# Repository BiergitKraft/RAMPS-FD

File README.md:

# RAMPS-FD

RAMPS for Due.

A RAMPS style Shield for Arduino Due to benefit from the 32bit uC combined with the modular Design of a RAMPS Board.
V2.3 adds SPI support by simply selecting it with a few jumpers.
V3.0 adds UART support. WIP

Status
-------

V2.3 tested and fuctional.
V3.0 WIP

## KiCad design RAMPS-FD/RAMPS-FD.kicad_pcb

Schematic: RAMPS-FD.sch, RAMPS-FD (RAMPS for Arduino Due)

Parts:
D2: LED_0603_GREEN; LED_0603
FID2, FID3, FID4: Fiducial; Fiducial_1mm_Mask2mm
J2: 2x1PinHeader; PinHeader_1x02_P2.54mm_Vertical
M2: LOGO_OSHW; OSHW_logo_2
Q2: NCE3416; SOT-23; Rating #20V #6.5A
R2: 330R; R_0603
SHIELD2: ARDUINO_DUE_SHIELD; ARDUINO_MEGA_DUE_SHIELD_FOOTPRINT_RMC
SW2: PushButton; SW_6x6_SMD

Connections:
+3V3: SHIELD2.3V3
+5V: D2.2; also elsewhere on the board
/E0_EN_BUF: SHIELD2.42; also elsewhere on the board
/E1_EN_BUF: SHIELD2.39; also elsewhere on the board
/E2_EN_BUF: SHIELD2.45; also elsewhere on the board
/RESET: J2.1, SHIELD2.RST, SW2.1
/X_EN_BUF: SHIELD2.48; also elsewhere on the board
/Y_EN_BUF: SHIELD2.46; also elsewhere on the board
/Z_EN_BUF: SHIELD2.44; also elsewhere on the board
A4: SHIELD2.AD4; also elsewhere on the board
A5: SHIELD2.AD5; also elsewhere on the board
A6: SHIELD2.AD6; also elsewhere on the board
A7: SHIELD2.AD7; also elsewhere on the board
AD14: SHIELD2.AD14; also elsewhere on the board
AD15: SHIELD2.AD15; also elsewhere on the board
AM-VIN: SHIELD2.V_IN; also elsewhere on the board
D2-FET6: SHIELD2.2; also elsewhere on the board
D8: SHIELD2.8; also elsewhere on the board
D9: SHIELD2.9; also elsewhere on the board
D10: SHIELD2.10; also elsewhere on the board
D11-FET4: SHIELD2.11; also elsewhere on the board
D12-FET5: SHIELD2.12; also elsewhere on the board
D13: Q2.1, SHIELD2.13
D23: SHIELD2.23; also elsewhere on the board
D25: SHIELD2.25; also elsewhere on the board
D27: SHIELD2.27; also elsewhere on the board
D29: SHIELD2.29; also elsewhere on the board
D31: SHIELD2.31; also elsewhere on the board
D32: SHIELD2.32; also elsewhere on the board
D33: SHIELD2.33; also elsewhere on the board
D35: SHIELD2.35; also elsewhere on the board
D37: SHIELD2.37; also elsewhere on the board
D41: SHIELD2.41; also elsewhere on the board
D43: SHIELD2.43; also elsewhere on the board
D47: SHIELD2.47; also elsewhere on the board
D49: SHIELD2.49; also elsewhere on the board
D50-MISO: SHIELD2.50; also elsewhere on the board
D51-MOSI: SHIELD2.51; also elsewhere on the board
D52-SCK: SHIELD2.52; also elsewhere on the board
DUE_5V: SHIELD2.5V; also elsewhere on the board
E0_DIR: SHIELD2.28; also elsewhere on the board
E0_STEP: SHIELD2.36; also elsewhere on the board
ESTOP: SHIELD2.40; also elsewhere on the board
GND: J2.2, Q2.2, SHIELD2.GND, SHIELD2.GND6, SW2.2; also elsewhere on the board
GNDA: SHIELD2.GND4, SHIELD2.GND5; also elsewhere on the board
IOREF: SHIELD2.IORF; also elsewhere on the board
MISO: SHIELD2.MISO; also elsewhere on the board
MOSI: SHIELD2.MOSI; also elsewhere on the board
unnamed: D2.1, R2.1
unnamed: Q2.3, R2.2
PS-ON: SHIELD2.53; also elsewhere on the board
SCK: SHIELD2.SCK; also elsewhere on the board
SCL: SHIELD2.21; also elsewhere on the board
SCL1: SHIELD2.SCL1; also elsewhere on the board
SDA: SHIELD2.20; also elsewhere on the board
SDA1: SHIELD2.SDA1; also elsewhere on the board
SERVO1: SHIELD2.7; also elsewhere on the board
SERVO2: SHIELD2.6; also elsewhere on the board
SERVO3: SHIELD2.5; also elsewhere on the board
SERVO4: SHIELD2.3; also elsewhere on the board
SPI_CS1: SHIELD2.4; also elsewhere on the board
THERM0: SHIELD2.AD0; also elsewhere on the board
THERM1: SHIELD2.AD1; also elsewhere on the board
THERM2: SHIELD2.AD2; also elsewhere on the board
THERM3: SHIELD2.AD3; also elsewhere on the board
UART0_RX_LV: SHIELD2.0; also elsewhere on the board
UART0_TX_LV: SHIELD2.1; also elsewhere on the board
UART1_RX_LV: SHIELD2.19; also elsewhere on the board
UART1_TX_LV: SHIELD2.18; also elsewhere on the board
UART2_RX_LV: SHIELD2.17; also elsewhere on the board
UART2_TX_LV: SHIELD2.16; also elsewhere on the board
UART3_RX_LV: SHIELD2.15; also elsewhere on the board
UART3_TX_LV: SHIELD2.14; also elsewhere on the board
X-MAX: SHIELD2.30; also elsewhere on the board
X-MIN: SHIELD2.22; also elsewhere on the board
X_DIR: SHIELD2.AD8; also elsewhere on the board
X_STEP: SHIELD2.AD9; also elsewhere on the board
Y-MAX: SHIELD2.38; also elsewhere on the board
Y-MIN: SHIELD2.24; also elsewhere on the board
Y_DIR: SHIELD2.AD10; also elsewhere on the board
Y_STEP: SHIELD2.AD11; also elsewhere on the board
Z-MAX: SHIELD2.34; also elsewhere on the board
Z-MIN: SHIELD2.26; also elsewhere on the board
Z_DIR: SHIELD2.AD12; also elsewhere on the board
Z_STEP: SHIELD2.AD13; also elsewhere on the board

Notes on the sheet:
Also used by Programming USB port
X/Y/Z pins are on single port for both Mega and Due
Reset
Status LED
LED

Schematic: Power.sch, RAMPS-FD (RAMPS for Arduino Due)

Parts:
C2: 100u_35V; CP_Elec_6.3x7.7; Rating #100uF #35V #20%
C3, C4: 100n; C_0603; Rating #100nF #50V #5%
D3, D4: KDZVTR11B; D_SOD-123F
D5: MRA4003T3G; D_SMA; Rating #300V #1A
F2, F3, F4: Keystone_3568; Fuseholder_Blade_Mini_Keystone_3568; Rating #500V #30A
F5, F6: FUSE_750mA_0603; R_0603; Rating #32V #750mA
J3: 6_PinScrewPlugableTerminal_P508; 6x1_P508_RA
J4: NetTie_1mm; TIE-1MM
J5, J7: 1x3JumperArray; PinHeader_1x03_P2.54mm_Vertical
J6: 2x1PinHeader; PinHeader_1x02_P2.54mm_Vertical
J8: 1x3PinHeader; PinHeader_1x03_P2.54mm_Vertical
JP2, JP3: 1x2JumperArray; PinHeader_1x02_P2.54mm_Vertical
Q3, Q4: TDM3415; SO-8_3.9x4.9mm_P1.27mm
R3, R4: 10k; R_0603
U2: AS7812ADTR; TO-252-2; Rating #12V #35V #1A

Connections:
+5V: J7.3, J8.1, JP3.2; also elsewhere on the board
+12P: D5.2, J5.2, J6.1; also elsewhere on the board
+V_HEATBED: F2.2; also elsewhere on the board
+V_LOGIC: J7.2; also elsewhere on the board
+V_MOTOR: D3.1, Q3.1, Q3.2, Q3.3; also elsewhere on the board
+V_POWER: C2.1, C3.1, D4.1, J5.3, Q4.1, Q4.2, Q4.3, U2.1; also elsewhere on the board
/Power/HB_IN: F2.1, J3.1
/Power/LP_1: D5.1, JP2.1
/Power/LP_2: C4.1, J5.1, U2.3
/Power/MOT_IN: F3.1, J3.5
/Power/P_IN: F4.1, J3.3
AM-VIN: JP2.2; also elsewhere on the board
DUE_5V: F6.2; also elsewhere on the board
GND: J6.2, J8.3; also elsewhere on the board
IOREF: F5.2; also elsewhere on the board
MOT_GND: C2.2, C3.2, C4.2, J3.2, J3.4, J3.6, R3.2, R4.2, U2.2; also elsewhere on the board
unnamed: D3.2, Q3.4, R3.1
unnamed: D4.2, Q4.4, R4.1
unnamed: F3.2, Q3.5, Q3.6, Q3.7, Q3.8
unnamed: F4.2, Q4.5, Q4.6, Q4.7, Q4.8
unnamed: F5.1, J7.1
unnamed: F6.1, JP3.1
PS-ON: J8.2; also elsewhere on the board

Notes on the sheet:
JP102 - VSEL - Select voltage 1-2 = POWER_IN = 24 V (or > 15V) 2-3 = POWER_IN = 12 V (or < 15V)
Low power MOSFETS (fans etc) also input to Due/Mega
Aux Power output
VLOG - Select logic voltage 1-2 = Autoselect by IOREF 2-3 = 5V
Medium power MOSFETS (extruder heaters, fans)
Heatbed Only: 12-24V, 15A
Motors only, 12-24V
Power
JP1: Supply 12V to Arduino in standalone operation Remove if Arduino is powered by USB or other supply
Note: use thick traces for all high power connections
12V or 24V input (ensure to set JP102 correctly!)
5V: External or Standby
Arduino base board
Note: On R3 compatible Arduinos, IOREF will supply 3.3V (Due), or 5V (Mega). If IOREF is not provided (non-R3) then it must be a 5V Arduino so set VLOG to 5V.
Capacitors rated to at least 25V unless otherwise stated

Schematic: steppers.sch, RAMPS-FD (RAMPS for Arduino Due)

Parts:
C5, C6, C7: 100u_35V; CP_Elec_6.3x7.7; Rating #100uF #35V #20%
D6, D8, D10: DS110W; D_SOD-123F
D7, D9, D11: SMF36CA; D_SOD-123F
J9, J10, J11, J12: 1x4PinHeader; pin_header_2.54mm_1x4
JP4, JP6, JP8: 4x3JumperArray; 4x3_2.54mm_Header
JP5, JP7, JP9: 1x2JumperArray; PinHeader_1x02_P2.54mm_Vertical
R5: 1k; R_0603
R6, R8, R10: 10k; R_0603
R7, R9, R11: 100k; R_0603
U3, U4, U5: Pololu; POLOLU
VR2, VR3, VR4, VR5, VR6, VR7, VR8, VR9, VR10, VR11, VR12, VR13, VR14, VR15, VR16, VR17, VR18, VR19: 33V; R_0603

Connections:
+5V: D6.2, D8.2, D10.2; also elsewhere on the board
+V_LOGIC: JP4.3, JP4.6, JP4.9, JP4.12, JP6.3, JP6.6, JP6.9, JP6.12, JP8.3, JP8.6, JP8.9, JP8.12, R6.1, R8.1, R10.1, U3.10, U4.10, U5.10; also elsewhere on the board
+V_MOTOR: C5.1, C6.1, C7.1, D6.1, D7.1, D8.1, D9.1, D10.1, D11.1, U3.16, U4.16, U5.16; also elsewhere on the board
/Stepper Drivers/X-1A: J9.3, U3.12, VR3.1, VR6.1
/Stepper Drivers/X-1B: J9.4, U3.11, VR3.2, VR7.1
/Stepper Drivers/X-2A: J9.2, U3.13, VR2.2, VR4.1
/Stepper Drivers/X-2B: J9.1, U3.14, VR2.1, VR5.1
/Stepper Drivers/Y-1A: J10.3, U4.12, VR10.1, VR13.1
/Stepper Drivers/Y-1B: J10.4, U4.11, VR11.1, VR13.2
/Stepper Drivers/Y-2A: J10.2, U4.13, VR8.1, VR12.2
/Stepper Drivers/Y-2B: J10.1, U4.14, VR9.1, VR12.1
/Stepper Drivers/Z-1A: J11.3, J12.3, U5.12, VR16.1, VR19.1
/Stepper Drivers/Z-1B: J11.4, J12.4, U5.11, VR17.1, VR19.2
/Stepper Drivers/Z-2A: J11.2, J12.2, U5.13, VR14.1, VR18.2
/Stepper Drivers/Z-2B: J11.1, J12.1, U5.14, VR15.1, VR18.1
/X_EN_BUF: U3.1; also elsewhere on the board
/Y_EN_BUF: U4.1; also elsewhere on the board
/Z_EN_BUF: U5.1; also elsewhere on the board
A6: JP8.7; also elsewhere on the board
A7: JP6.7; also elsewhere on the board
AD15: JP4.7; also elsewhere on the board
D50-MISO: JP4.10, JP6.10, JP8.10; also elsewhere on the board
D51-MOSI: JP4.1, JP6.1, JP8.1; also elsewhere on the board
D52-SCK: JP4.4, JP6.4, JP8.4; also elsewhere on the board
GND: R7.2, R9.2, R11.2, U3.9, U4.9, U5.9; also elsewhere on the board
MOT_GND: C5.2, C6.2, C7.2, D7.2, D9.2, D11.2, U3.15, U4.15, U5.15, VR4.2, VR5.2, VR6.2, VR7.2, VR8.2, VR9.2, VR10.2, VR11.2, VR14.2, VR15.2, VR16.2, VR17.2; also elsewhere on the board
unnamed: JP4.2, R7.1, U3.2
unnamed: JP4.5, U3.3
unnamed: JP4.8, U3.4
unnamed: JP4.11, JP5.2, U3.5
unnamed: JP6.2, R9.1, U4.2
unnamed: JP6.5, U4.3
unnamed: JP6.8, U4.4
unnamed: JP6.11, JP7.2, U4.5
unnamed: JP8.2, R11.1, U5.2
unnamed: JP8.5, U5.3
unnamed: JP8.8, U5.4
unnamed: JP8.11, JP9.2, U5.5
unnamed: R6.2, U3.6
unnamed: R8.2, U4.6
unnamed: R10.2, U5.6
UART1_RX_LV: JP5.1, JP7.1, JP9.1, R5.1; also elsewhere on the board
UART1_TX_LV: R5.2; also elsewhere on the board
X_DIR: U3.8; also elsewhere on the board
X_STEP: U3.7; also elsewhere on the board
Y_DIR: U4.8; also elsewhere on the board
Y_STEP: U4.7; also elsewhere on the board
Z_DIR: U5.8; also elsewhere on the board
Z_STEP: U5.7; also elsewhere on the board

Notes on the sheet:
Add jumpers for TMC2130 SPI
Use Jumpers to Connect the SPI Bus to your Stepperdrivers, for example for TMC 2130, or to select the microstepping for your Pololu by connecting the middle pin row to +V_Logic

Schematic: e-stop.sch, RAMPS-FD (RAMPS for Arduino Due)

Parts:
C8: 100n; C_0603; Rating #100nF #50V #5%
D12: 2CZ4007; D_SOD-123F; Rating #1kV #1A
D13: LED_0603_GREEN; LED_0603
J13: 2x1PinHeader; PinHeader_1x02_P2.54mm_Vertical
Q5: NCE3416; SOT-23; Rating #20V #6.5A
R12: 100k; R_0603
R13: 4k7; R_0603
R14: 330R; R_0603
RP2, RP3, RP4: 10kArrayx4; R_Array_Convex_4x0603
U6: SN74LV1T125; SOT-23-5

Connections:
+5V: C8.1, R14.1, U6.5; also elsewhere on the board
+V_LOGIC: R12.1, RP2.5, RP2.6, RP2.7, RP2.8, RP3.7, RP3.8; also elsewhere on the board
/E0_EN_BUF: RP2.4; also elsewhere on the board
/E1_EN_BUF: RP3.1; also elsewhere on the board
/E2_EN_BUF: RP3.2; also elsewhere on the board
/X_EN_BUF: RP2.1; also elsewhere on the board
/Y_EN_BUF: RP2.2; also elsewhere on the board
/Z_EN_BUF: RP2.3; also elsewhere on the board
D2-FET6: RP4.8; also elsewhere on the board
D8: RP3.4, U6.2; also elsewhere on the board
D8_BUF: U6.4; also elsewhere on the board
D9: RP3.3; also elsewhere on the board
D10: RP4.7; also elsewhere on the board
D11-FET4: RP4.6; also elsewhere on the board
D12-FET5: RP4.5; also elsewhere on the board
ESTOP: D12.1; also elsewhere on the board
GND: C8.2, Q5.2, R13.2, RP3.5, RP3.6, RP4.1, RP4.2, RP4.3, RP4.4, U6.3; also elsewhere on the board
unnamed: D12.2, J13.1, Q5.1, R12.2, U6.1
unnamed: D13.1, Q5.3
unnamed: D13.2, R14.2
unnamed: J13.2, R13.1

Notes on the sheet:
Emergency Stop switch (Normally Closed type) use jumper to bypass
Or any small signal diode
Active low
Active high
Use a Buffer to translate the 3V3 Signal of the Due to 5V to fully open the Mosfet Possible alternative parts (pin compatible): 74LVC1G17 SN74LV1T34

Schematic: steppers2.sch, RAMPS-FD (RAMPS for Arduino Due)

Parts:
C9, C10, C11: 100u_35V; CP_Elec_6.3x7.7; Rating #100uF #35V #20%
D14, D16, D18: DS110W; D_SOD-123F
D15, D17, D19: SMF36CA; D_SOD-123F
J14, J15, J16: 1x4PinHeader; pin_header_2.54mm_1x4
JP10, JP12, JP14: 4x3JumperArray; 4x3_2.54mm_Header
JP11, JP13, JP15: 1x2JumperArray; PinHeader_1x02_P2.54mm_Vertical
R15: 1k; R_0603
R16, R18, R20: 10k; R_0603
R17, R19, R21: 100k; R_0603
U7, U8, U9: Pololu; POLOLU
VR20, VR21, VR22, VR23, VR24, VR25, VR26, VR27, VR28, VR29, VR30, VR31, VR32, VR33, VR34, VR35, VR36, VR37: 33V; R_0603

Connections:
+5V: D14.2, D16.2, D18.2; also elsewhere on the board
+V_LOGIC: JP10.3, JP10.6, JP10.9, JP10.12, JP12.3, JP12.6, JP12.9, JP12.12, JP14.3, JP14.6, JP14.9, JP14.12, R16.1, R18.1, R20.1, U7.10, U8.10, U9.10; also elsewhere on the board
+V_MOTOR: C9.1, C10.1, C11.1, D14.1, D15.1, D16.1, D17.1, D18.1, D19.1, U7.16, U8.16, U9.16; also elsewhere on the board
/E0_EN_BUF: U7.1; also elsewhere on the board
/E1_EN_BUF: U8.1; also elsewhere on the board
/E2_EN_BUF: U9.1; also elsewhere on the board
/Stepper Drivers 2/E0-1A: J14.3, U7.12, VR21.1, VR24.1
/Stepper Drivers 2/E0-1B: J14.4, U7.11, VR21.2, VR25.1
/Stepper Drivers 2/E0-2A: J14.2, U7.13, VR20.2, VR22.1
/Stepper Drivers 2/E0-2B: J14.1, U7.14, VR20.1, VR23.1
/Stepper Drivers 2/E1-1A: J15.3, U8.12, VR27.1, VR30.1
/Stepper Drivers 2/E1-1B: J15.4, U8.11, VR27.2, VR31.1
/Stepper Drivers 2/E1-2A: J15.2, U8.13, VR26.2, VR29.1
/Stepper Drivers 2/E1-2B: J15.1, U8.14, VR26.1, VR28.1
/Stepper Drivers 2/E2-1A: J16.3, U9.12, VR34.1, VR37.1
/Stepper Drivers 2/E2-1B: J16.4, U9.11, VR35.1, VR37.2
/Stepper Drivers 2/E2-2A: J16.2, U9.13, VR33.1, VR36.2
/Stepper Drivers 2/E2-2B: J16.1, U9.14, VR32.1, VR36.1
A4: JP10.7; also elsewhere on the board
A5: JP12.7; also elsewhere on the board
AD14: JP14.7; also elsewhere on the board
D32: U9.7; also elsewhere on the board
D41: U8.8; also elsewhere on the board
D43: U8.7; also elsewhere on the board
D47: U9.8; also elsewhere on the board
D50-MISO: JP10.10, JP12.10, JP14.10; also elsewhere on the board
D51-MOSI: JP10.1, JP12.1, JP14.1; also elsewhere on the board
D52-SCK: JP10.4, JP12.4, JP14.4; also elsewhere on the board
E0_DIR: U7.8; also elsewhere on the board
E0_STEP: U7.7; also elsewhere on the board
GND: R17.2, R19.2, R21.2, U7.9, U8.9, U9.9; also elsewhere on the board
MOT_GND: C9.2, C10.2, C11.2, D15.2, D17.2, D19.2, U7.15, U8.15, U9.15, VR22.2, VR23.2, VR24.2, VR25.2, VR28.2, VR29.2, VR30.2, VR31.2, VR32.2, VR33.2, VR34.2, VR35.2; also elsewhere on the board
unnamed: JP10.2, R17.1, U7.2
unnamed: JP10.5, U7.3
unnamed: JP10.8, U7.4
unnamed: JP10.11, JP11.2, U7.5
unnamed: JP12.2, R19.1, U8.2
unnamed: JP12.5, U8.3
unnamed: JP12.8, U8.4
unnamed: JP12.11, JP13.2, U8.5
unnamed: JP14.2, R21.1, U9.2
unnamed: JP14.5, U9.3
unnamed: JP14.8, U9.4
unnamed: JP14.11, JP15.2, U9.5
unnamed: R16.2, U7.6
unnamed: R18.2, U8.6
unnamed: R20.2, U9.6
UART1_RX_LV: JP11.1; also elsewhere on the board
UART2_RX_LV: JP13.1, JP15.1, R15.2; also elsewhere on the board
UART2_TX_LV: R15.1; also elsewhere on the board

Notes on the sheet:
Add jumpers for TMC2130 SPI
Use Jumpers to Connect the SPI Bus to your Stepperdrivers, for example for TMC 2130, or to select the microstepping for your Pololu by connecting the middle pin row to +V_Logic

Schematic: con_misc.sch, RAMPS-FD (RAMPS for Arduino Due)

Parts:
C12: 100n; C_0603; Rating #100nF #50V #5%
J17, J20: 1x3PinHeader; PinHeader_1x03_P2.54mm_Vertical
J18: 2x5PinHeader; pin_header_2.54mm_2x5
J19, J22: 1x4PinHeader; pin_header_2.54mm_1x4
J21: 2x6PinHeader; pin_header_2.54mm_2x6
J23: 3x4PinHeader; 4x3_2.54mm_Header
J24: 1x18PinHeader; PinHeader_1x18_P2.54mm_Vertical
R22, R23, R24, R25: 10k; R_0603
U10: 24C512; SOIC-8_3.9x4.9mm_P1.27mm

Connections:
+5V: J21.1, J23.2, J23.5, J23.8, J23.11; also elsewhere on the board
+V_LOGIC: C12.1, J18.1, J19.1, J21.12, J22.1, J24.1, R22.1, R23.1, R24.1, R25.1, U10.8 (VCC); also elsewhere on the board
/E1_EN_BUF: J24.8; also elsewhere on the board
/E2_EN_BUF: J24.5; also elsewhere on the board
A4: J18.3; also elsewhere on the board
A5: J18.4; also elsewhere on the board
A6: J18.5; also elsewhere on the board
A7: J18.6; also elsewhere on the board
AD14: J18.7; also elsewhere on the board
AD15: J18.8; also elsewhere on the board
D23: J24.16; also elsewhere on the board
D25: J24.15; also elsewhere on the board
D27: J24.14; also elsewhere on the board
D29: J24.13; also elsewhere on the board
D31: J24.12; also elsewhere on the board
D32: J24.3; also elsewhere on the board
D33: J24.11; also elsewhere on the board
D35: J24.10; also elsewhere on the board
D37: J24.9; also elsewhere on the board
D41: J24.7; also elsewhere on the board
D43: J24.6; also elsewhere on the board
D47: J24.4; also elsewhere on the board
D49: J21.2; also elsewhere on the board
D50-MISO: J21.9; also elsewhere on the board
D51-MOSI: J21.10; also elsewhere on the board
D52-SCK: J21.11; also elsewhere on the board
GND: C12.2, J17.1, J18.2, J19.2, J20.1, J21.7, J22.2, J23.1, J23.4, J23.7, J23.10, J24.2, U10.1 (A0), U10.2 (A1), U10.3 (A2), U10.4 (GND), U10.7 (WP); also elsewhere on the board
MISO: J21.3; also elsewhere on the board
MOSI: J21.4; also elsewhere on the board
SCK: J21.5; also elsewhere on the board
SCL: J19.4, R22.2, U10.6 (SCL); also elsewhere on the board
SCL1: J22.4, R24.2; also elsewhere on the board
SDA: J19.3, R23.2, U10.5 (SDA); also elsewhere on the board
SDA1: J22.3, R25.2; also elsewhere on the board
SERVO1: J23.3; also elsewhere on the board
SERVO2: J23.6; also elsewhere on the board
SERVO3: J23.9; also elsewhere on the board
SERVO4: J23.12; also elsewhere on the board
SPI_CS1: J21.6; also elsewhere on the board
UART0_RX_LV: J17.2; also elsewhere on the board
UART0_TX_LV: J17.3; also elsewhere on the board
UART1_RX_LV: J20.2; also elsewhere on the board
UART1_TX_LV: J20.3; also elsewhere on the board
UART2_RX_LV: J24.17; also elsewhere on the board
UART2_TX_LV: J24.18; also elsewhere on the board
UART3_RX_LV: J18.10; also elsewhere on the board
UART3_TX_LV: J18.9; also elsewhere on the board

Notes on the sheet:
Serial
UART-TTL
Must not have external pullups to 5V if IOREF = 3.3V
1k5 Pull ups on Due
Aux3 - SPI
Aux2
Aux connectors
Servos
I2C
NB: On Arduino Due: IOs on this page are not 5V tolerant. Do not exceed 3.3V.
Note: this serial port is shared with USB programming port
These are shared with E1 and E2 stepper signals
Mega: same signals as MISO, MOSI & SCK
NB This pin is always 5V
These are free for LCD panel etc
Note: Some addon boards connect this pin to GND.
EEPROM
Might want to allow other addresses
Aux4 - general IO

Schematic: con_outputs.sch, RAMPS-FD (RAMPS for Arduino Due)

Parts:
D20, D21, D24, D25: MRA4003T3G; D_SMA; Rating #300V #1A
D22, D23, D26, D27: LED_0603_RED; LED_0603
J25, J27, J28: 2_PinScrewTerminal_P350; 2x1_P350
J26: 2_PinScrewTerminal_P508; 2x1_P508
Q6, Q8, Q9: PSMN7R5-60YLX; LFPAK56; Rating #60V #86A
Q7: PSMN1R8-40YLC; LFPAK56; Rating #40V #100A
R26, R27, R30, R31: 1k; R_0603
R28, R29, R32, R33: 33R; R_0603

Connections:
+V_HEATBED: D21.1, J26.1, R27.1; also elsewhere on the board
+V_POWER: D20.1, D24.1, D25.1, J25.1, J27.1, J28.1, R26.1, R30.1, R31.1; also elsewhere on the board
/Mosfet Outputs/D8_OUT: D21.2, D23.1, J26.2, Q7.5
/Mosfet Outputs/D9_OUT: D24.2, D26.1, J27.2, Q9.5
/Mosfet Outputs/D10_OUT: D25.2, D27.1, J28.2, Q8.5
/Mosfet Outputs/FET4_OUT: D20.2, D22.1, J25.2, Q6.5
D8_BUF: R29.1; also elsewhere on the board
D9: R33.1; also elsewhere on the board
D10: R32.1; also elsewhere on the board
D11-FET4: R28.1; also elsewhere on the board
MOT_GND: Q6.1, Q6.2, Q6.3, Q7.1, Q7.2, Q7.3, Q8.1, Q8.2, Q8.3, Q9.1, Q9.2, Q9.3; also elsewhere on the board
unnamed: D22.2, R26.2
unnamed: D23.2, R27.2
unnamed: D26.2, R30.2
unnamed: D27.2, R31.2
unnamed: Q6.4, R28.2
unnamed: Q7.4, R29.2
unnamed: Q8.4, R32.2
unnamed: Q9.4, R33.2

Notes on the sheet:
FET4 - Extruder 3 / Fan
D10 - Extruder 2 / Fan
D9 - Extruder 1
D8 - Heatbed
Non-inverting drivers
MOSFET Outputs
Or similar

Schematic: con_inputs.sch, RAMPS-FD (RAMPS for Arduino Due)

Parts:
C13: 100n; C_0603; Rating #100nF #50V #5%
J29: 3x6PinHeader; 6x3_2.54mm_Header
JP16: 1x2JumperArray; PinHeader_1x02_P2.54mm_Vertical
RP5, RP6: 10kArrayx4; R_Array_Convex_4x0603
U11: MC74LCX07; TSSOP-14_4.4x5mm_P0.65mm

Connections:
+5V: J29.1, J29.4, J29.7, J29.10, J29.13, J29.16, JP16.1; also elsewhere on the board
+V_LOGIC: C13.1, U11.14; also elsewhere on the board
GND: C13.2, J29.3, J29.6, J29.9, J29.12, J29.15, J29.18, U11.7; also elsewhere on the board
unnamed: J29.2, RP5.4, U11.1
unnamed: J29.5, RP5.3, U11.3
unnamed: J29.8, RP5.2, U11.5
unnamed: J29.11, RP6.3, U11.13
unnamed: J29.14, RP6.2, U11.11
unnamed: J29.17, RP6.1, U11.9
unnamed: JP16.2, RP5.5, RP5.6, RP5.7, RP5.8, RP6.5, RP6.6, RP6.7, RP6.8
X-MAX: U11.10; also elsewhere on the board
X-MIN: U11.8; also elsewhere on the board
Y-MAX: U11.6; also elsewhere on the board
Y-MIN: U11.12; also elsewhere on the board
Z-MAX: U11.2; also elsewhere on the board
Z-MIN: U11.4; also elsewhere on the board

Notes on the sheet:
Endstop inputs are 5V tolerant
Endstops
JP801 should be used to enable pullups for switch type endstops; remove for active types (e.g opto)

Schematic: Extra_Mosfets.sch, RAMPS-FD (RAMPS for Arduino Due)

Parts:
D28, D30: 2CZ4007; D_SOD-123F; Rating #1kV #1A
D29, D31: LED_0603_RED; LED_0603
J30, J31: 2x1PinHeader; PinHeader_1x02_P2.54mm_Vertical
Q10, Q11: NCE3416; SOT-23; Rating #20V #6.5A
R34, R36: 1k; R_0603
R35, R37: 33R; R_0603

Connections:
+12P: D28.1, D30.1, J30.1, J31.1, R34.1, R36.1; also elsewhere on the board
/Extra MOSFETs/P_FET5: D28.2, D29.1, J30.2, Q10.3
/Extra MOSFETs/P_FET6: D30.2, D31.1, J31.2, Q11.3
D2-FET6: R37.1; also elsewhere on the board
D12-FET5: R35.1; also elsewhere on the board
MOT_GND: Q10.2, Q11.2; also elsewhere on the board
unnamed: D29.2, R34.2
unnamed: D31.2, R36.2
unnamed: Q10.1, R35.2
unnamed: Q11.1, R37.2

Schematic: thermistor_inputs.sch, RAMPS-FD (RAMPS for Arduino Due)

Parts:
C14, C16, C18, C20: 100n; C_0603; Rating #100nF #50V #5%
C15, C17, C19, C21: 10u; C_0603; Rating #10uF #25V #10%
FB2: FB0603; R_0603; Rating #500mA #390Ohm@100MHz
J32: 2x4PinHeader_2.54mm; pin_header_2.54mm_2x4
R38, R39, R40, R41: 1k; R_0603

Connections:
+V_LOGIC: FB2.1; also elsewhere on the board
AREF: FB2.2, R38.1, R39.1, R40.1, R41.1
GNDA: C14.2, C15.2, C16.2, C17.2, C18.2, C19.2, C20.2, C21.2, J32.1, J32.3, J32.5, J32.7; also elsewhere on the board
THERM0: C14.1, C15.1, J32.2, R38.2; also elsewhere on the board
THERM1: C16.1, C17.1, J32.4, R39.2; also elsewhere on the board
THERM2: C18.1, C19.1, J32.6, R40.2; also elsewhere on the board
THERM3: C20.1, C21.1, J32.8, R41.2; also elsewhere on the board

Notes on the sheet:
To CPU
From thermistors
Thermistor Inputs

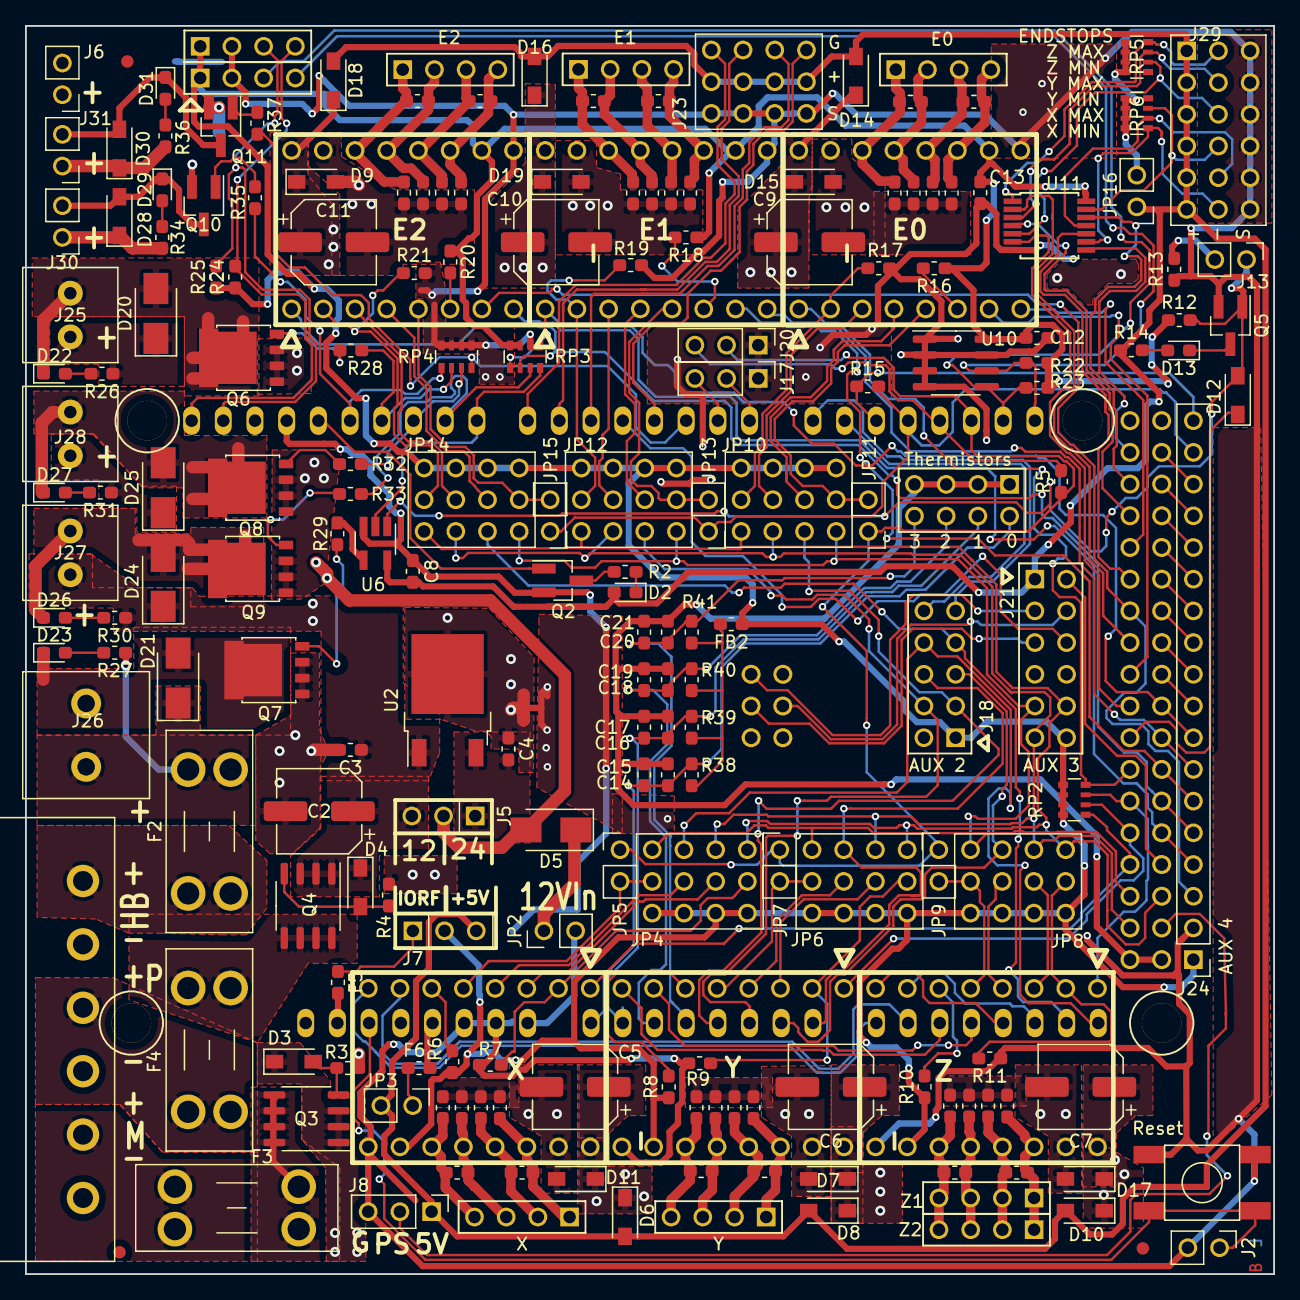
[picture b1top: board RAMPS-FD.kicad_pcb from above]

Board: 2 copper layers, 100.0 x 100.0 mm, 209 parts (1 on the bottom side), 186 nets.

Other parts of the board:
NT1: NetTie-2_SMD_Pad0.5mm

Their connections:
GND: NT1.2; also elsewhere on the board
MOT_GND: NT1.1; also elsewhere on the board

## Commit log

2020-03-24 Inital Commit RAMPS FD v2.3. SPI Support for every Driver added.
2020-06-07 Added UART for Communication with TMC2209 Drivers, improved inverse-polarity protection, added Driver Protection. Two Layer Design
2020-06-10 Lagenspiegel, minor Silkscreen
2020-08-26 V3 Added, UART support for steppers and improved parts/layout
2020-10-14 Bug Notice for Enstop Header

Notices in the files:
RAMPS-FD/Extra_Mosfets.sch:
GPL v3
